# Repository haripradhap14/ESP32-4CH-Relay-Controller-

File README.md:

# Smart Home Automation Controller (4-Channel Relay)

This project is a compact and integrated **Smart Home Automation Controller** designed using KiCad. It allows users to control household appliances remotely via Wi-Fi, leveraging the power of the ESP32-WROOM-32E module.

## 🚀 Key Features
* **Microcontroller:** ESP32-WROOM-32E (Integrated Wi-Fi & Bluetooth connectivity).
* **Power Management:**
    * Integrated AC-to-DC converter (230V AC to 5V DC).
    * High-efficiency 5V to 3.3V step-down regulator for stable power supply to the ESP32.
* **Control Unit:** 4-Channel Relay board to switch high-voltage home appliances (lights, fans, etc.).
* **Design:** Compact, single-board design suitable for wall-mount enclosures.
* **Flexibility:** The board is designed to be modular, allowing users to adapt inputs/switches based on specific smart home requirements.

## 🛠 Technical Specifications
* **Controller:** ESP32-WROOM-32E
* **Relay Channels:** 4 x High-quality relays with opto-isolation (for safety).
* **PCB Layers:** 2-Layer Board (FR4 material).
* **Design Software:** KiCad EDA.

## ⚠️ Safety Warning
This project involves dealing with **230V AC Mains voltage**. Please ensure all high-voltage connections are properly insulated and handled with extreme caution during testing and installation.

## 📂 Project Structure
* `/Schematic` - Contains the circuit design and architecture.
* `/PCB` - Contains the PCB layout (.kicad_pcb file).
* `/Gerbers` - Contains the manufacturing files (Gerber & Drill files) for PCB fabrication.

---
*Designed for home automation enthusiasts and IoT developers.*

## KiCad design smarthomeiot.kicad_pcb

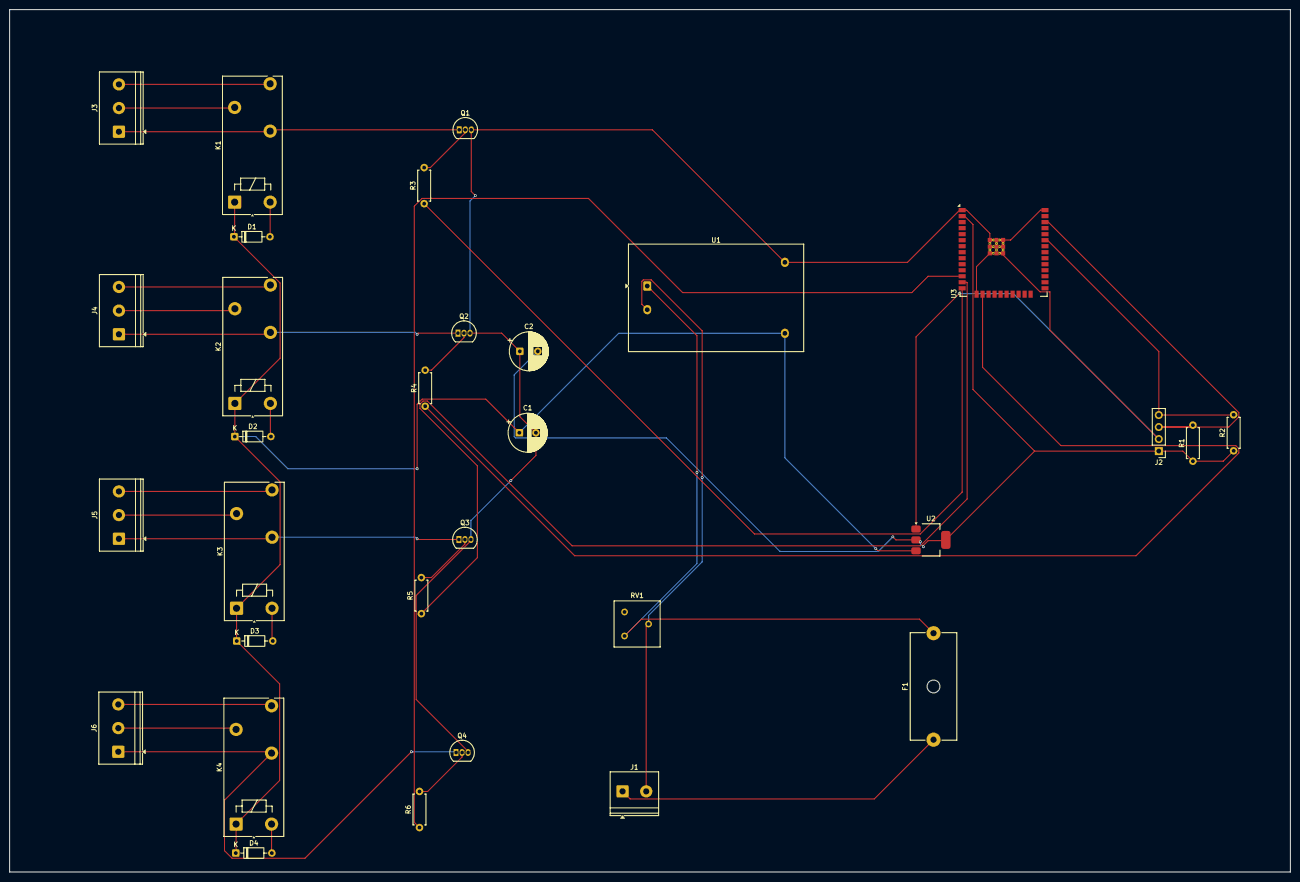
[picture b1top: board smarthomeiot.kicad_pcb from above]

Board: 2 copper layers, 270.6 x 182.2 mm, 31 parts (0 on the bottom side), 32 nets.

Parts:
C1: 470uF/25V; CP_Radial_D8.0mm_P3.50mm
C2: 100uF/16V; CP_Radial_D8.0mm_P3.80mm
D1, D2, D3, D4: 1N4148; D_DO-35_SOD27_P7.62mm_Horizontal
F1: 500mA-1A; Fuseholder_Cylinder-5x20mm_Schurter_0031_8201_Horizontal_Op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
J1: Screw_Terminal_01x02; TerminalBlock_Phoenix_PT-1,5-2-5.0-H_1x02_P5.00mm_Horizontal
J2: Conn_01x04_Socket; PinHeader_1x04_P2.54mm_Vertical
J3, J4, J5, J6: Screw_Terminal_01x03; TerminalBlock_Phoenix_PT-1,5-3-5.0-H_1x03_P5.00mm_Horizontal
K1, K2, K3, K4: Relay_SPDT; Relay_SPDT_Finder_40.51
Q1, Q2, Q3, Q4: BC547; TO-92_Inline
R1, R2, R3, R4, R5, R6: 1k; R_Axial_DIN0207_L6.3mm_D2.5mm_P7.62mm_Horizontal
RV1: 275V Varistor; Potentiometer_Bourns_3386F_Vertical
U1: HLK-PM01; Converter_ACDC_Hi-Link_HLK-PMxx
U2: AMS1117-3.3; SOT-223-3_TabPin2
U3: ESP32-WROOM-32E

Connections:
+3V3: C2.2, J2.1, R1.1, R2.1, U2.2 (VO), U3.2 (VDD)
+5V: C1.1, D1.1 (K), D2.1 (K), D3.1 (K), D4.1 (K), K1.A1, K2.A1, K3.A1, K4.A1, U1.4 (+Vout), U2.3 (VI)
/ESP32_Controller/Relay_1: R3.1, U3.14 (IO12)
/ESP32_Controller/Relay_2: R4.1, U3.16 (IO13)
/ESP32_Controller/Relay_3: R5.1, U3.13 (IO14)
/ESP32_Controller/Relay_4: R6.1, U3.12 (IO27)
GND: C1.2, C2.1, J2.2, Q1.3 (E), Q2.3 (E), Q3.3 (E), Q4.3 (E), U1.3 (-Vout), U2.1 (GND), U3.1 (GND), U3.15 (GND), U3.38 (GND), U3.39 (GND)
unnamed: D1.2 (A), K1.A2
unnamed: D2.2 (A), K2.A2
unnamed: D3.2 (A), K3.A2
unnamed: D4.2 (A), K4.A2
unnamed: F1.1, J1.1
unnamed: J1.2, RV1.2, U1.2 (AC/N)
unnamed: J2.3, R1.2, U3.36 (IO22)
unnamed: J2.4, R2.2, U3.33 (IO21)
unnamed: J3.1, K1.12, Q1.1 (C)
unnamed: J3.2, K1.11
unnamed: J3.3, K1.14
unnamed: J4.1, K2.12, Q2.1 (C)
unnamed: J4.2, K2.11
unnamed: J4.3, K2.14
unnamed: J5.1, K3.12, Q3.1 (C)
unnamed: J5.2, K3.11
unnamed: J5.3, K3.14
unnamed: J6.1, K4.12, Q4.1 (C)
unnamed: J6.2, K4.11
unnamed: J6.3, K4.14
unnamed: Q1.2 (B), R3.2
unnamed: Q2.2 (B), R4.2
unnamed: Q3.2 (B), R5.2
unnamed: Q4.2 (B), R6.2
unnamed: F1.2, RV1.1, U1.1 (AC/L)
